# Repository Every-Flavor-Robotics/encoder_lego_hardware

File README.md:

# encoder_go_hardware
hardware files for encoder go project

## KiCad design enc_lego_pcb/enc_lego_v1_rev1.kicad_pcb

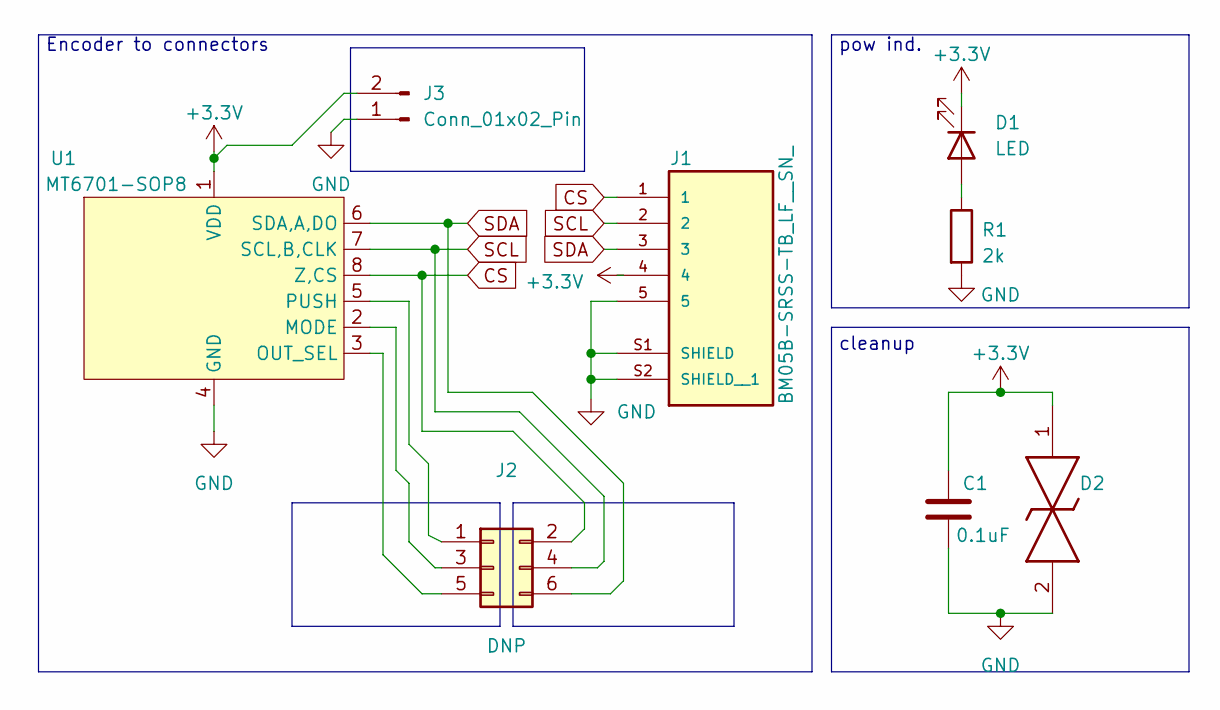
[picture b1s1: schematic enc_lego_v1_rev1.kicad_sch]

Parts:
C1: 0.1uF; C_0805_2012Metric_Pad1.18x1.45mm_HandSolder
D1: LED; D_0805_2012Metric
D2: SMAJ6.0CAe3_TR13; DIONM5025X225N; Mouser Part Number 494-SMAJ6.0CAE3/TR13
J1: BM05B-SRSS-TB_LF__SN_; JST_BM05B-SRSS-TB_LF__SN_; PARTREV N/A
J2: DNP; PinHeader_2x03_P2.54mm_Vertical
J3: Conn_01x02_Pin; PinHeader_1x02_P2.54mm_Vertical
R1: 2k; R_0805_2012Metric_Pad1.20x1.40mm_HandSolder
U1: MT6701-SOP8; MT6701_SOP8

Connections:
+3.3V: C1.1, D1.1 (K), D2.1, J1.4, J3.2, U1.1 (VDD)
CS: J1.1, J2.2, U1.8 (Z,CS)
GND: C1.2, D2.2, J1.5, J1.S1 (SHIELD), J1.S2 (SHIELD__1), J3.1, R1.2, U1.4 (GND)
unnamed: D1.2 (A), R1.1
unnamed: J2.1, U1.5 (PUSH)
unnamed: J2.3, U1.2 (MODE)
unnamed: J2.5, U1.3 (OUT_SEL)
SCL: J1.2, J2.4, U1.7 (SCL,B,CLK)
SDA: J1.3, J2.6, U1.6 (SDA,A,DO)

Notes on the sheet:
pow ind.
Encoder to connectors
cleanup

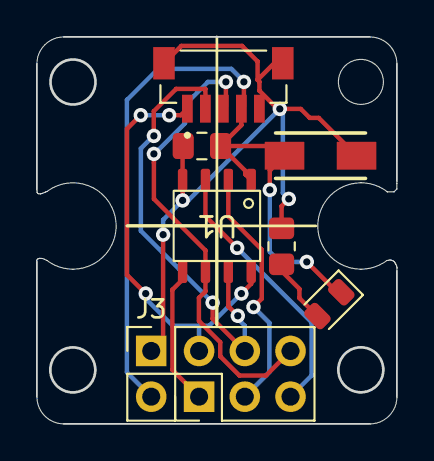
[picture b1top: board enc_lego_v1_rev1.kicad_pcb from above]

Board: 2 copper layers, 20.0 x 21.4 mm, 8 parts (0 on the bottom side), 9 nets.

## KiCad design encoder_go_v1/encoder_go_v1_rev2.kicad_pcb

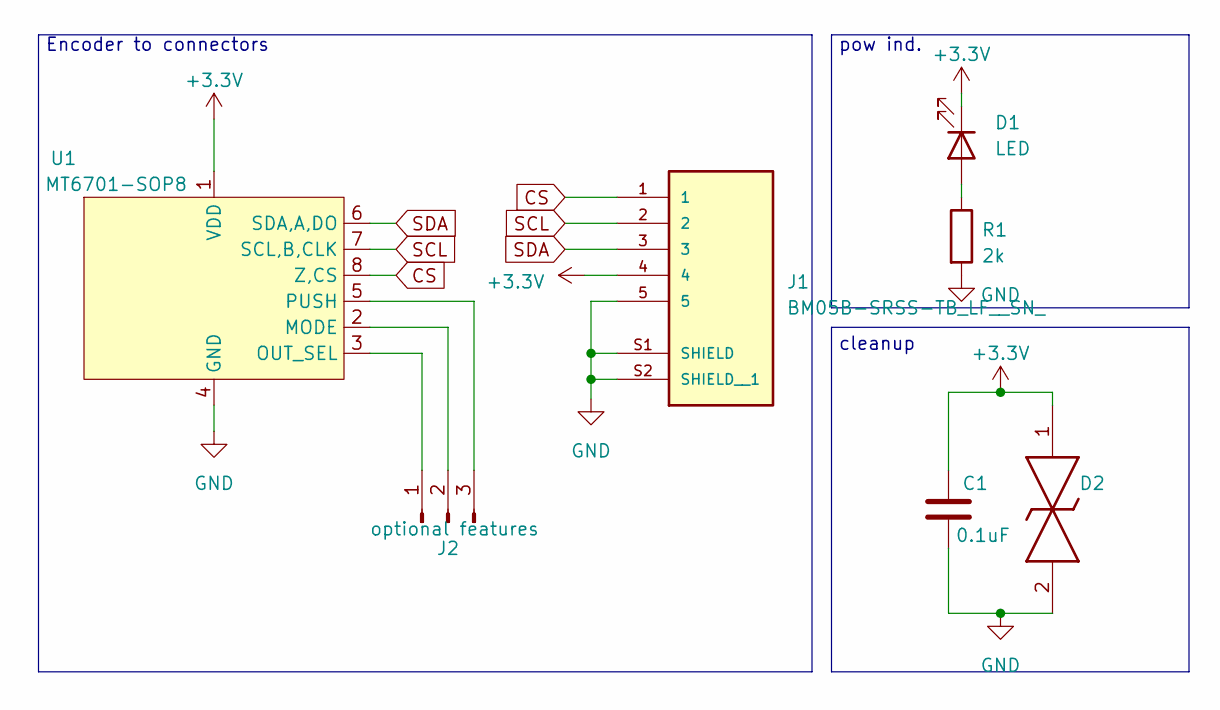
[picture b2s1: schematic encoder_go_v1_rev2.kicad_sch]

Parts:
C1: 0.1uF; C_0805_2012Metric_Pad1.18x1.45mm_HandSolder
D1: LED; D_0805_2012Metric
D2: SMAJ6.0CAe3_TR13; DIONM5025X225N; Mouser Part Number 494-SMAJ6.0CAE3/TR13
J1: BM05B-SRSS-TB_LF__SN_; JST_BM05B-SRSS-TB_LF__SN_; PARTREV N/A
J2: optional features; PinHeader_1x03_P2.54mm_Horizontal
R1: 2k; R_0805_2012Metric_Pad1.20x1.40mm_HandSolder
U1: MT6701-SOP8; MT6701_SOP8

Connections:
+3.3V: C1.1, D1.1 (K), D2.1, J1.4, U1.1 (VDD)
CS: J1.1, U1.8 (Z,CS)
GND: C1.2, D2.2, J1.5, J1.S1 (SHIELD), J1.S2 (SHIELD__1), R1.2, U1.4 (GND)
unnamed: D1.2 (A), R1.1
unnamed: J2.1, U1.3 (OUT_SEL)
unnamed: J2.2, U1.2 (MODE)
unnamed: J2.3, U1.5 (PUSH)
SCL: J1.2, U1.7 (SCL,B,CLK)
SDA: J1.3, U1.6 (SDA,A,DO)

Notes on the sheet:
pow ind.
Encoder to connectors
cleanup

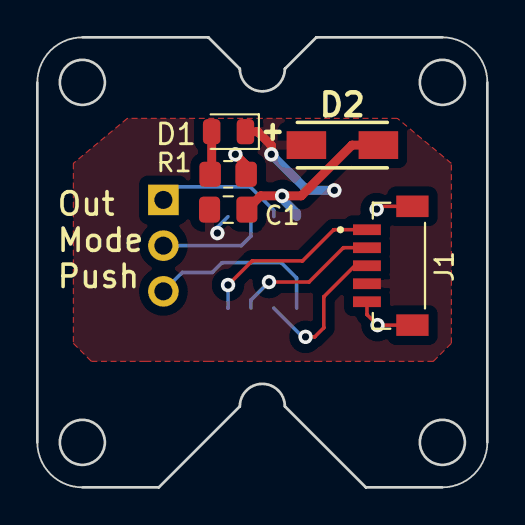
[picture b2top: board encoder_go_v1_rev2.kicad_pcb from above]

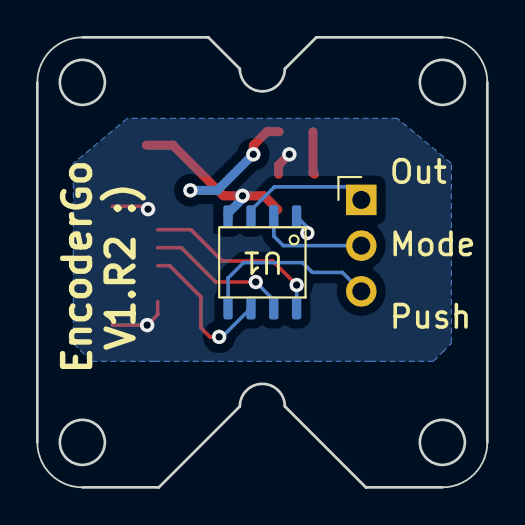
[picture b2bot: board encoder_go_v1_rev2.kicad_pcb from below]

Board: 2 copper layers, 25.0 x 25.0 mm, 7 parts (2 on the bottom side), 9 nets.

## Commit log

2023-12-15 messy first commit with panel
2024-06-04 add encoder lego board to repo
2024-06-04 copy and modify encodergo for lego
2024-06-04 updated BOM for order TS
